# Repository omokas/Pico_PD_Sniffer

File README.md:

# Pico PD Sniffer

This project is a helpful tool to analyze USB Power Delivery signals using the RP2040 microcontroller and sigrok PulseView software  

The PCB is designed to be compatible with RP2040 Zero boards only  

## Software / Firmware

Download sigrok PulseView for your OS from the following link  
https://sigrok.org/wiki/Downloads

Sigrok firmware for RP2040 is provided in the following repository  
https://github.com/pico-coder/sigrok-pico/tree/main/pico_sdk_sigrok/build

## Credits
Orestis Mokas - PCB Design  
pico-coder    - RP2040 Pico Sigrok firmware  
wolfgangfriedrich - [USB PD - CC decoding adventures](https://community.element14.com/technologies/power-management/b/blog/posts/usb-pd---cc-decoding-adventures)

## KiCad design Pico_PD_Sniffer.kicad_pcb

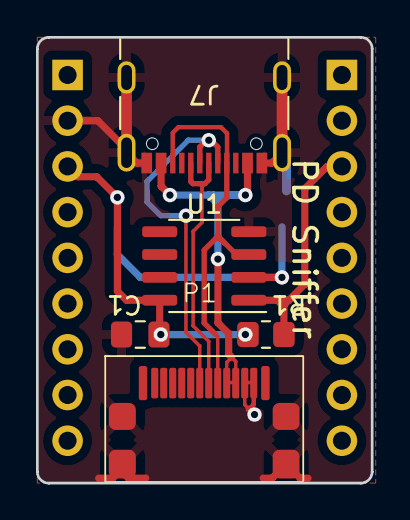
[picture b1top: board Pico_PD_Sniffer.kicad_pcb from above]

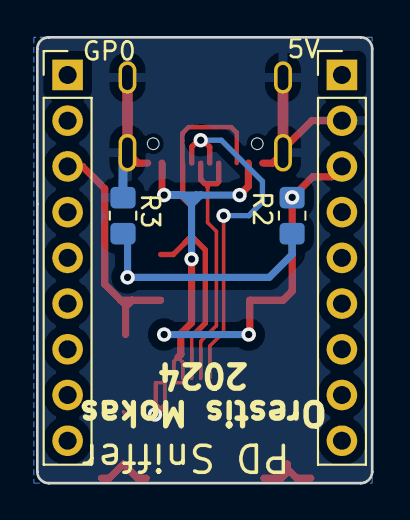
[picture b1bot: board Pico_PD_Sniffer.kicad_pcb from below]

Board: 2 copper layers, 18.6 x 24.8 mm, 9 parts (4 on the bottom side), 8 nets.

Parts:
5V: Conn_01x09; PinHeader_1x09_P2.54mm_Vertical
C1: 100nF; C_0805_2012Metric_Pad1.18x1.45mm_HandSolder
GP0: Conn_01x09; PinHeader_1x09_P2.54mm_Vertical
J7: USB_C_Receptacle_USB2.0; USB_C_Receptacle_GCT_USB4105-xx-A_16P_TopMnt_Horizontal
P1: USB_C_Plug_USB2.0; USB_C_male_12P
R1: 470R; R_0805_2012Metric_Pad1.20x1.40mm_HandSolder
R2: 12K; R_0805_2012Metric_Pad1.20x1.40mm_HandSolder
R3: 1.8K; R_0805_2012Metric_Pad1.20x1.40mm_HandSolder
U1: LM393; SOIC-8_3.9x4.9mm_P1.27mm

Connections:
+3V3: 5V.3, C1.2, R1.1, R2.1, U1.8 (V+)
CC1: J7.A5 (CC1), J7.B5 (CC2), P1.A5 (CC), U1.3 (+)
CC1_OUT: GP0.3, R1.2, U1.1
DM_1: J7.A7 (D-), J7.B7 (D-), P1.A7 (D-)
DP_1: J7.A6 (D+), J7.B6 (D+), P1.A6 (D+)
GND: 5V.2, C1.1, J7.A1 (GND), J7.A12 (GND), J7.B1 (GND), J7.B12 (GND), J7.S1 (SHIELD), P1.A1 (GND), P1.B12 (GND), P1.S1 (SHIELD), R3.2, U1.4 (V-)
unnamed: R2.2, R3.1, U1.2 (-)
VBUS: J7.A4 (VBUS), J7.A9 (VBUS), J7.B4 (VBUS), J7.B9 (VBUS), P1.A4 (VBUS), P1.B9 (VBUS)

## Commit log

2025-08-23 Add Kicad Project files
    Requires Kicad 7.0 or later
